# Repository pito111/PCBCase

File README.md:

# PCB Case

This is designed to take an KICad 7 `.kicad_pcb` file and produce an openscad file that is the case.

The problem is that you need 3D models for your parts for this to work sensibly, so the C code has a list of footprints as basic openscad outlines. This is not like the 3D models in KiCad which are accurate, it is simply boxes and shapes that allow for the 3D box to have a sensibly sized cut out for the part.
In many cases this means the model is just a cuboid. But in some cases it is slightly more important as it has the attached connector included.

Any parts of the design that would breach the case cause cut outs and supports in the case surround.

Parts like LEDs can have holes through the case so they are visible, etc.

## models

Modules are individual scad instructions, and can be named as the first match of :-

- The footprint name (without `prefix:`)
- The footprint name (without `prefix:`) where single numeric component is replaced with `0`
- The 3D model name(s) in the footprint

The module is called with `pushed` and `hulled` which are Boolean, and in the case of the `0` version, with `n` which is the number that was replaced with 0.

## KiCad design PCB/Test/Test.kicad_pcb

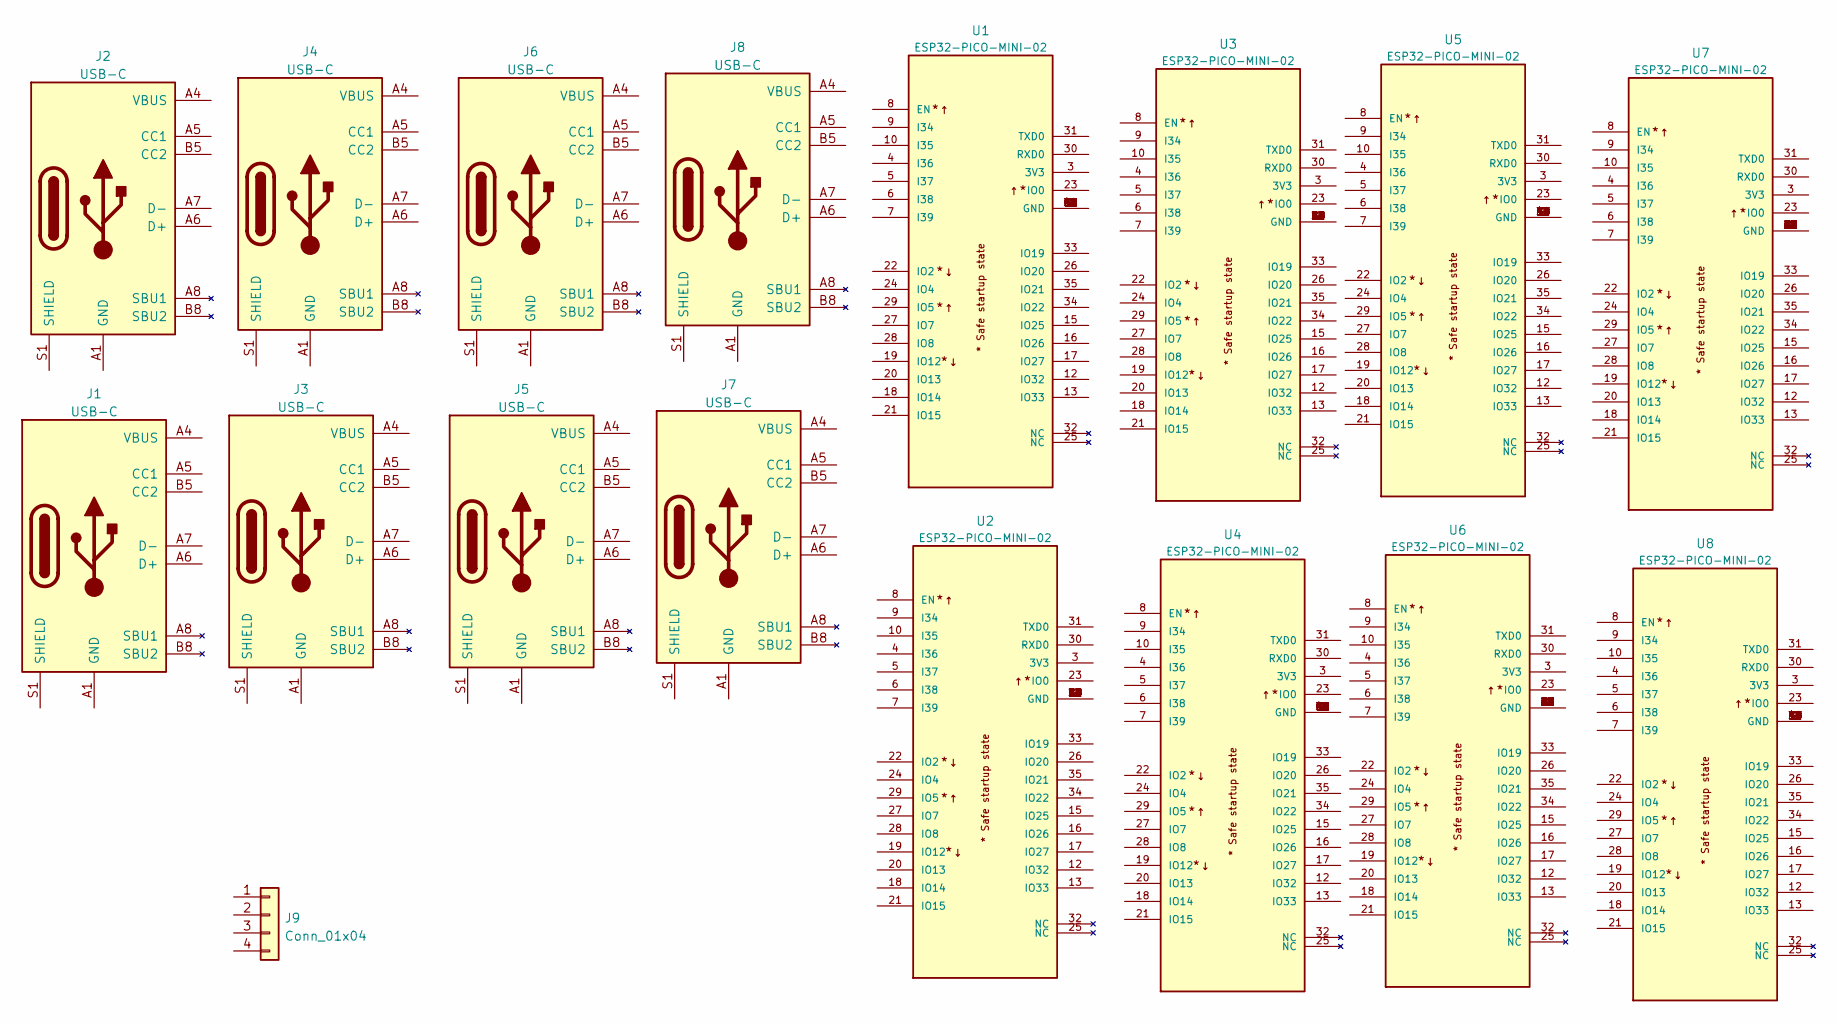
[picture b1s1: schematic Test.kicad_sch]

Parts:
J1, J2, J3, J4, J5, J6, J7, J8: USB-C; USC16-TR-Round
J9: Conn_01x04; JLC-PinHeader_1x04_P2.54mm_Right
U1, U2, U3, U4, U5, U6, U7, U8: ESP32-PICO-MINI-02; PARTREV v1.0

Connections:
unnamed: J1.A1 (GND), J1.A12 (GND), J1.B1 (GND), J1.B12 (GND)
unnamed: J1.A4 (VBUS), J1.A9 (VBUS), J1.B4 (VBUS), J1.B9 (VBUS)
unnamed: J1.A6 (D+), J1.B6 (D+)
unnamed: J1.A7 (D-), J1.B7 (D-)
unnamed: J2.A1 (GND), J2.A12 (GND), J2.B1 (GND), J2.B12 (GND)
unnamed: J2.A4 (VBUS), J2.A9 (VBUS), J2.B4 (VBUS), J2.B9 (VBUS)
unnamed: J2.A6 (D+), J2.B6 (D+)
unnamed: J2.A7 (D-), J2.B7 (D-)
unnamed: J3.A1 (GND), J3.A12 (GND), J3.B1 (GND), J3.B12 (GND)
unnamed: J3.A4 (VBUS), J3.A9 (VBUS), J3.B4 (VBUS), J3.B9 (VBUS)
unnamed: J3.A6 (D+), J3.B6 (D+)
unnamed: J3.A7 (D-), J3.B7 (D-)
unnamed: J4.A1 (GND), J4.A12 (GND), J4.B1 (GND), J4.B12 (GND)
unnamed: J4.A4 (VBUS), J4.A9 (VBUS), J4.B4 (VBUS), J4.B9 (VBUS)
unnamed: J4.A6 (D+), J4.B6 (D+)
unnamed: J4.A7 (D-), J4.B7 (D-)
unnamed: J5.A1 (GND), J5.A12 (GND), J5.B1 (GND), J5.B12 (GND)
unnamed: J5.A4 (VBUS), J5.A9 (VBUS), J5.B4 (VBUS), J5.B9 (VBUS)
unnamed: J5.A6 (D+), J5.B6 (D+)
unnamed: J5.A7 (D-), J5.B7 (D-)
unnamed: J6.A1 (GND), J6.A12 (GND), J6.B1 (GND), J6.B12 (GND)
unnamed: J6.A4 (VBUS), J6.A9 (VBUS), J6.B4 (VBUS), J6.B9 (VBUS)
unnamed: J6.A6 (D+), J6.B6 (D+)
unnamed: J6.A7 (D-), J6.B7 (D-)
unnamed: J7.A1 (GND), J7.A12 (GND), J7.B1 (GND), J7.B12 (GND)
unnamed: J7.A4 (VBUS), J7.A9 (VBUS), J7.B4 (VBUS), J7.B9 (VBUS)
unnamed: J7.A6 (D+), J7.B6 (D+)
unnamed: J7.A7 (D-), J7.B7 (D-)
unnamed: J8.A1 (GND), J8.A12 (GND), J8.B1 (GND), J8.B12 (GND)
unnamed: J8.A4 (VBUS), J8.A9 (VBUS), J8.B4 (VBUS), J8.B9 (VBUS)
unnamed: J8.A6 (D+), J8.B6 (D+)
unnamed: J8.A7 (D-), J8.B7 (D-)
unnamed: U1.1 (GND), U1.2 (GND), U1.11 (GND), U1.14 (GND), U1.36 (GND), U1.37 (GND), U1.38 (GND), U1.39 (GND), U1.40 (GND), U1.41 (GND), U1.42 (GND), U1.43 (GND), U1.44 (GND), U1.45 (GND), U1.46 (GND), U1.47 (GND), U1.48 (GND), U1.49 (GND), U1.50 (GND), U1.51 (GND), U1.52 (GND), U1.53 (GND)
unnamed: U2.1 (GND), U2.2 (GND), U2.11 (GND), U2.14 (GND), U2.36 (GND), U2.37 (GND), U2.38 (GND), U2.39 (GND), U2.40 (GND), U2.41 (GND), U2.42 (GND), U2.43 (GND), U2.44 (GND), U2.45 (GND), U2.46 (GND), U2.47 (GND), U2.48 (GND), U2.49 (GND), U2.50 (GND), U2.51 (GND), U2.52 (GND), U2.53 (GND)
unnamed: U3.1 (GND), U3.2 (GND), U3.11 (GND), U3.14 (GND), U3.36 (GND), U3.37 (GND), U3.38 (GND), U3.39 (GND), U3.40 (GND), U3.41 (GND), U3.42 (GND), U3.43 (GND), U3.44 (GND), U3.45 (GND), U3.46 (GND), U3.47 (GND), U3.48 (GND), U3.49 (GND), U3.50 (GND), U3.51 (GND), U3.52 (GND), U3.53 (GND)
unnamed: U4.1 (GND), U4.2 (GND), U4.11 (GND), U4.14 (GND), U4.36 (GND), U4.37 (GND), U4.38 (GND), U4.39 (GND), U4.40 (GND), U4.41 (GND), U4.42 (GND), U4.43 (GND), U4.44 (GND), U4.45 (GND), U4.46 (GND), U4.47 (GND), U4.48 (GND), U4.49 (GND), U4.50 (GND), U4.51 (GND), U4.52 (GND), U4.53 (GND)
unnamed: U5.1 (GND), U5.2 (GND), U5.11 (GND), U5.14 (GND), U5.36 (GND), U5.37 (GND), U5.38 (GND), U5.39 (GND), U5.40 (GND), U5.41 (GND), U5.42 (GND), U5.43 (GND), U5.44 (GND), U5.45 (GND), U5.46 (GND), U5.47 (GND), U5.48 (GND), U5.49 (GND), U5.50 (GND), U5.51 (GND), U5.52 (GND), U5.53 (GND)
unnamed: U6.1 (GND), U6.2 (GND), U6.11 (GND), U6.14 (GND), U6.36 (GND), U6.37 (GND), U6.38 (GND), U6.39 (GND), U6.40 (GND), U6.41 (GND), U6.42 (GND), U6.43 (GND), U6.44 (GND), U6.45 (GND), U6.46 (GND), U6.47 (GND), U6.48 (GND), U6.49 (GND), U6.50 (GND), U6.51 (GND), U6.52 (GND), U6.53 (GND)
unnamed: U7.1 (GND), U7.2 (GND), U7.11 (GND), U7.14 (GND), U7.36 (GND), U7.37 (GND), U7.38 (GND), U7.39 (GND), U7.40 (GND), U7.41 (GND), U7.42 (GND), U7.43 (GND), U7.44 (GND), U7.45 (GND), U7.46 (GND), U7.47 (GND), U7.48 (GND), U7.49 (GND), U7.50 (GND), U7.51 (GND), U7.52 (GND), U7.53 (GND)
unnamed: U8.1 (GND), U8.2 (GND), U8.11 (GND), U8.14 (GND), U8.36 (GND), U8.37 (GND), U8.38 (GND), U8.39 (GND), U8.40 (GND), U8.41 (GND), U8.42 (GND), U8.43 (GND), U8.44 (GND), U8.45 (GND), U8.46 (GND), U8.47 (GND), U8.48 (GND), U8.49 (GND), U8.50 (GND), U8.51 (GND), U8.52 (GND), U8.53 (GND)

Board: 2 copper layers, 17 parts (8 on the bottom side), 40 nets, no tracks yet.

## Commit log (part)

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2019-11-25 Default
2019-11-25 New case
2019-11-26 click
2019-11-26 Tweak
2019-11-26 Arrrg
2019-11-26 Edge
2019-11-26 Correct SMA connector
2019-11-26 Audio
2019-11-27 Iffy
2019-11-27 Silly
2019-11-28 Added cutin()
2019-11-28 Neater GSM2 Click
2019-11-28 solder
2019-11-28 Tidier, I think
2019-11-29 Tweak spox
2019-11-29 Tweak defaults
2019-12-03 1220 is bigger
2019-12-04 Glue gun
2019-12-04 SPOX issues
2019-12-04 Typo
2021-03-14 Start on new KiCad based case design
2021-03-14 Starting new code
2021-03-14 Started on logic
2021-03-14 Well, we seem to be parsing, now the hard part
2021-03-14 PCB outline */
2021-03-14 Basic logic working, now making models
2021-03-14 Fix flip
2021-03-14 Sort y direction
2021-03-14 Some usable models
2021-03-14 Started on cae workings
2021-03-14 6 wat
2021-03-14 Tidy
2021-03-14 Moved
2021-03-14 Rework
2021-03-14 Defaults
2021-03-14 Arrg, still not right!
2021-03-14 Maybe working now
2021-03-14 Messy
2021-03-14 Edges
2021-03-14 Fix minkowski error
2021-03-14 Allow for some solder
2021-03-14 Borders
2021-03-14 Simpler
2021-03-14 Specify edge
2021-03-15 Ignore
2021-03-15 Timd
2021-03-15 Offset
2021-03-15 D'Oh
2021-03-15 Adjust
2021-03-15 Reposition
2021-03-15 Position
2021-03-15 Default 0 fit
2021-03-15 Tidy clearances
2021-03-15 Broke minkowski again
2021-03-15 More cut to function
2021-03-15 Corners tidy
2021-03-15 Other components clash too
2021-03-15 Spacing
2021-03-15 Fix spacing parts
2021-03-15 fit default
2021-03-15 Allow raised parts inside
2021-03-15 Air hole
2021-03-15 Electrical blank plate (UK) with screw holes
2021-03-16 Comment
2021-03-16 Extra arg to allow for holes, etc that do not need to be pushed
2021-03-16 Minor tweaks
2021-03-16 Smaller edge by default
2021-03-16 Move hole
2021-03-16 Hole size issues?
2021-03-16 OLED hole fix
2021-03-16 Holes not big enough
2021-03-17 More air holes
2021-03-17 Tweak height
2021-03-17 Size
2021-03-17 Better
2021-03-18 Screws
2021-03-25 --inside-offset
2021-03-25 Bigger screw holes
2021-03-25 Adjust clearances
2021-03-26 Header
2021-04-11 More for C
2021-04-11 More space for C
2021-04-24 QFN20
2021-04-29 Handle rounded corners!
2021-04-29 For now
2021-04-29 Start
2021-04-29 Simply modules
2021-04-29 Tolerances already handled
2021-04-29 Tidy the logic for non rectangular PCBs
2021-05-01 More models
2021-05-01 Link
2021-05-01 Faster
2021-05-02 More bits
2021-05-02 0805
2021-05-02 Added TYA4020
2021-05-02 Hull the inside
2021-05-02 Neater
2021-05-02 --no-render
2021-05-02 base/top in code not final.scad now
2021-05-03 Tweak R
2021-05-03 More
2021-05-03 Tweaked for solder
2021-05-03 Tidier
2021-05-03 Fix overlap (especially an issue with thin boards)
2021-05-03 Rounded corners!
2021-05-04 Change margin default
2021-05-04 Local override size
2021-05-04 Stupid arc error
2021-05-04 Max width
2021-05-04 Handle origin
2021-05-05 Change margin
2021-05-05 Fix overlap issues
2021-05-06 New switch
2021-06-17 Extra models
2021-06-20 COrrect
2021-07-17 Wrong way around
2021-07-18 Hole for LED
2021-07-19 Tweak curves
2021-08-05 Try that
2021-08-07 Tweak headers
2021-08-07 Control curves
2022-01-31 KiCad 6
2022-01-31 Starting point
2022-02-08 Button
2022-02-08 Grrr, centred on pin 1?
2022-02-08 Position of 3D model
2022-03-02 SImple
2022-03-03 New ESP
2022-03-03 Match 3D model
2022-03-03 Cropped pins
2022-03-03 Fix LED
2022-03-07 New edge feature
2022-03-07 Ooops
2022-03-07 Test
2022-03-07 Multiple oiutlines
2022-03-07 Holes
2022-03-07 Battery
2022-03-07 --no-hull
2022-03-08 Allow user edge non hull
2022-03-09 Air holes
2022-03-09 Curves for KiCad6
2022-03-09 Format
2022-03-09 Edge case
2022-03-09 New edge settings
2022-03-09 Try that?
2022-03-09 Need to fix arcs
2022-03-09 Arcs
2022-03-09 Finally
2022-03-09 Check 360?
2022-03-09 Tidy odd shapes
2022-03-09 Still tinkering
2022-03-09 Avoid PCb face
2022-03-09 Debug
2022-03-10 Grrr
2022-03-10 Hull edge
2022-03-10 Back
2022-03-10 PCB mounting
2022-03-10 Adjust lip
2022-03-11 Weird
2022-05-20 In practice these connectors touch, so don't leave a gap
2022-05-20 Longer
2022-05-20 The gaps were not there anyway, D'Oh
2022-05-21 OLED screws
2022-05-21 Report not closed
2022-05-21 Location
2022-06-11 Re read data sheet
2022-06-11 Tidy LED
2022-06-17 Tamper stuff
2022-06-17 Tinker
2022-06-17 Legs
2022-06-17 Tamper
2022-06-17 Trying to allow zero margin stuff e.g. for exact tamper switch
2022-06-17 Pips
2022-06-17 Height is not 4
2022-06-17 Not tight enough
2022-06-17 Too far
2022-06-21 tracklen started
2022-06-21 Track len checker on footprints
2022-06-21 Spiral generator
2022-06-29 Start on embedded footprint outlines
2022-06-29 More models and footprint tweaks
2022-06-29 Tweaks
2022-06-30 Was right anyway
2022-07-04 Screw
2022-07-04 Slotted
2022-08-05 detection switches
2022-08-06 Tighter tolerances for tamper
2022-08-06 Orientation
2022-08-06 Tolerance
2022-08-06 No need for tighter
2022-08-06 Posn
2022-08-06 Clearance
2022-08-22 PinHeader_1x05_P2.54mm_Vertical_SMD_Pin1Right.scad
2022-10-06 Might be X backwards
2022-10-06 Wide opening
2022-10-06 Middle ground
2022-12-19 Backwards?
2023-01-09 L_1210
2023-01-10 Issue with rotate order, needs careful testing
2023-01-10 Test files
2023-01-10 Tide
2023-01-10 rotate direction
2023-01-10 Obvious really
2023-01-19 Pins
2023-02-07 7 pin
2023-02-07 Cleaner
2023-02-07 Even more
2023-02-07 Slightly bigger
2023-02-07 Tweak size
2023-02-08 Origins fix
2023-02-08 user edge fixes
2023-03-26 Updated test case
2023-03-26 Working on footprint level 3D options
2023-03-26 Closer
2023-03-26 Should have footprint level logic now
2023-03-26 New logic
2023-03-26 indent
2023-03-26 Adjust for footprint level
2023-03-26 Same with lugs
2023-03-26 White version of same connector
2023-03-26 White version
2023-03-27 digits after -
2023-03-31 JST EH
2023-04-04 SOIC8
2023-04-05 Another SOIC8
2023-04-19 first match
2023-04-19 again
2023-04-19 find xN first
2023-04-24 Pin headers
2023-04-24 Fix orientation
2023-05-01 Tiny sensor
2023-05-01 iHole
2023-05-01 M3.5
2023-06-22 popt changes
2023-07-01 --panel
2023-07-01 Changed to User.N for custom pcb and case border
2023-08-02 Leads
2023-08-15 Fix S3
2023-08-31 Diode
2023-09-02 New LED
